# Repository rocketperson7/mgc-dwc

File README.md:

# mgc-dwc
Make Good Collective Digital White Cane

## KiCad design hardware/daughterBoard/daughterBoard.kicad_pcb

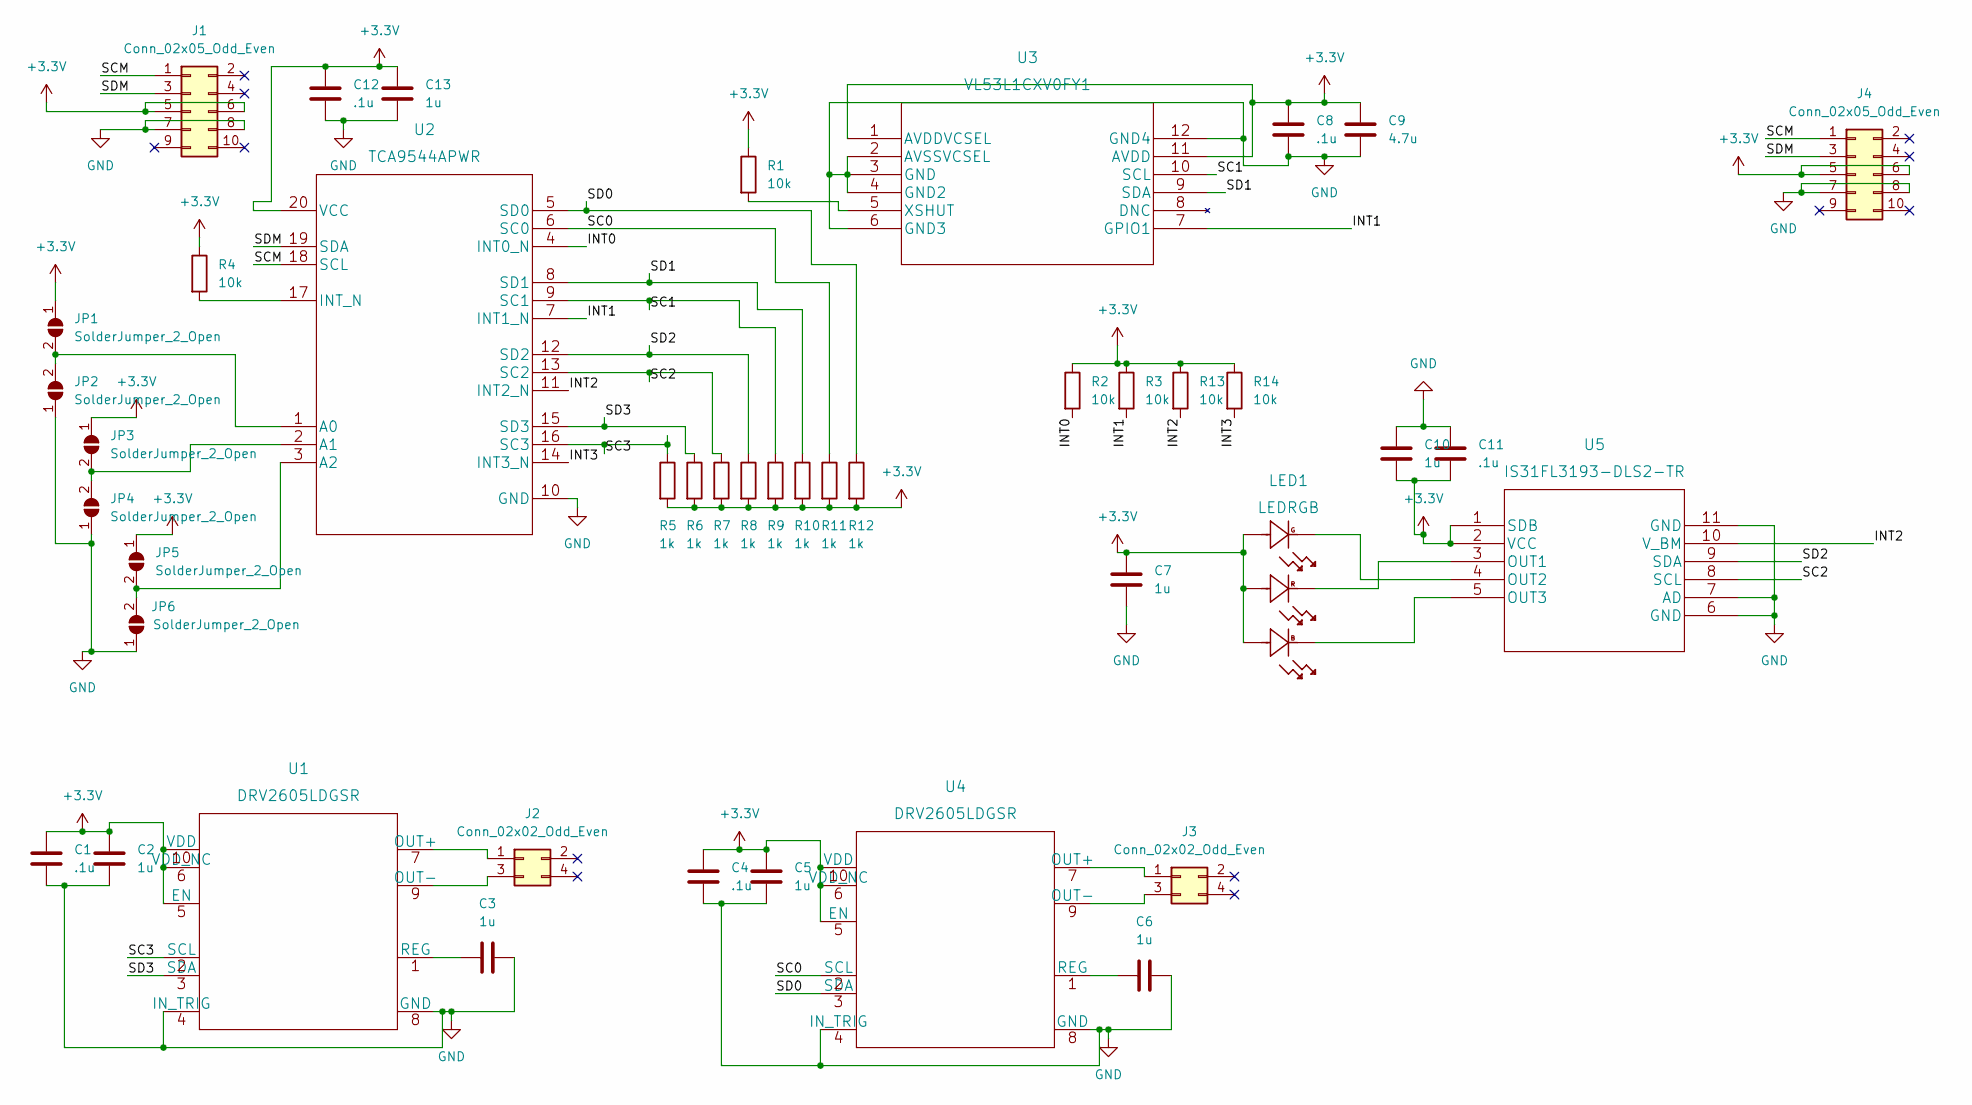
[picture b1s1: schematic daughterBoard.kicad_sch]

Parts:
C1, C4, C8, C11, C12: .1u; C_01005_0402Metric_Pad0.57x0.30mm_HandSolder
C2, C3, C5, C6, C7, C10, C13: 1u; C_01005_0402Metric_Pad0.57x0.30mm_HandSolder
C9: 4.7u; C_01005_0402Metric_Pad0.57x0.30mm_HandSolder
J1, J4: Conn_02x05_Odd_Even; PinHeader_2x05_P1.27mm_Vertical
J2, J3: Conn_02x02_Odd_Even; PinHeader_2x02_P2.54mm_Vertical
JP1, JP2, JP3, JP4, JP5, JP6: SolderJumper_2_Open; SolderJumper-2_P1.3mm_Open_TrianglePad1.0x1.5mm
LED1: LEDRGB; 150352M173300
R1, R2, R3, R4, R13, R14: 10k; R_01005_0402Metric_Pad0.57x0.30mm_HandSolder
R5, R6, R7, R8, R9, R10, R11, R12: 1k; R_01005_0402Metric_Pad0.57x0.30mm_HandSolder
U1, U4: DRV2605LDGSR
U2: TCA9544APWR
U3: VL53L1CXV0FY1; VL53L1CXV0FY&slash_1
U5: IS31FL3193-DLS2-TR

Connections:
+3V3: C1.1, C2.1, C4.1, C5.1, C7.1, C8.1, C9.1, C10.2, C11.2, C12.1, C13.1, J1.5, J1.6, J4.5, J4.6, JP1.1 (A), JP3.1 (A), JP5.1 (A), LED1.2, LED1.4, LED1.6, R1.1, R2.1, R3.1, R4.1, R5.2, R6.2, R7.2, R8.2, R9.2, R10.2, R11.2, R12.2, R13.1, R14.1, U1.5 (EN), U1.6 (VDD_NC), U1.10 (VDD), U2.20 (VCC), U3.1 (AVDDVCSEL), U3.11 (AVDD), U4.5 (EN), U4.6 (VDD_NC), U4.10 (VDD), U5.1 (SDB), U5.2 (VCC)
/INT0: R2.2, U2.4 (INT0_N)
/INT1: R3.2, U2.7 (INT1_N), U3.7 (GPIO1)
/INT2: R13.2, U2.11 (INT2_N), U5.10 (V_BM)
/INT3: R14.2, U2.14 (INT3_N)
/SC0: R11.1, U2.6 (SC0), U4.2 (SCL)
/SC1: R9.1, U2.9 (SC1), U3.10 (SCL)
/SC2: R7.1, U2.13 (SC2), U5.8 (SCL)
/SC3: R5.1, U1.2 (SCL), U2.16 (SC3)
/SCM: J1.1, J4.1, U2.18 (SCL)
/SD0: R12.1, U2.5 (SD0), U4.3 (SDA)
/SD1: R10.1, U2.8 (SD1), U3.9 (SDA)
/SD2: R8.1, U2.12 (SD2), U5.9 (SDA)
/SD3: R6.1, U1.3 (SDA), U2.15 (SD3)
/SDM: J1.3, J4.3, U2.19 (SDA)
GND: C1.2, C2.2, C3.2, C4.2, C5.2, C6.2, C7.2, C8.2, C9.2, C10.1, C11.1, C12.2, C13.2, J1.7, J1.8, J4.7, J4.8, JP2.1 (A), JP4.1 (A), JP6.1 (A), U1.4 (IN_TRIG), U1.8 (GND), U2.10 (GND), U3.2 (AVSSVCSEL), U3.3 (GND), U3.4 (GND2), U3.6 (GND3), U3.12 (GND4), U4.4 (IN_TRIG), U4.8 (GND), U5.6 (GND), U5.7 (AD), U5.11 (GND)
unnamed: C3.1, U1.1 (REG)
unnamed: C6.1, U4.1 (REG)
unnamed: J2.1, U1.7 (OUT+)
unnamed: J2.3, U1.9 (OUT-)
unnamed: J3.1, U4.7 (OUT+)
unnamed: J3.3, U4.9 (OUT-)
unnamed: JP1.2 (B), JP2.2 (B), U2.1 (A0)
unnamed: JP3.2 (B), JP4.2 (B), U2.2 (A1)
unnamed: JP5.2 (B), JP6.2 (B), U2.3 (A2)
unnamed: R1.2, U3.5 (XSHUT)
unnamed: R4.2, U2.17 (INT_N)
unnamed: LED1.3, U5.3 (OUT1)
unnamed: LED1.5, U5.4 (OUT2)
unnamed: LED1.1, U5.5 (OUT3)

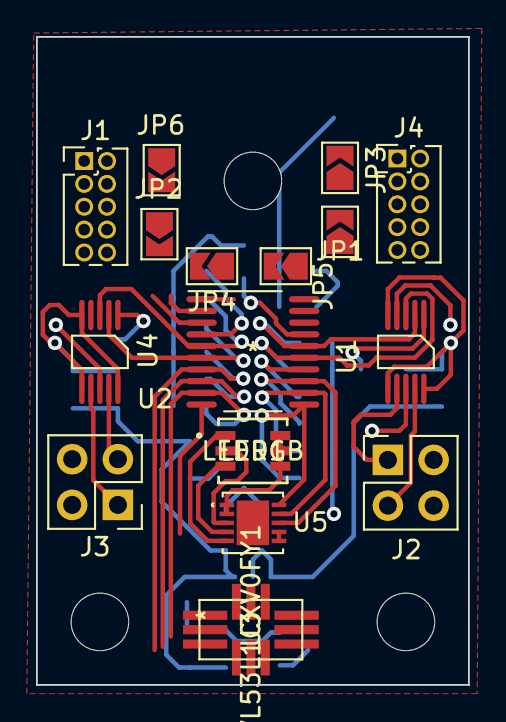
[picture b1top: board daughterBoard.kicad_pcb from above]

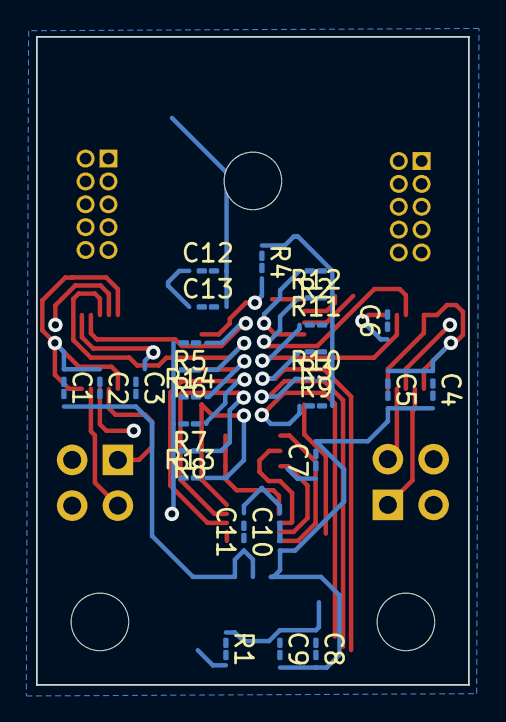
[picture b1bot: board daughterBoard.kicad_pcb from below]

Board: 4 copper layers, 24.0 x 36.0 mm, 43 parts (27 on the bottom side), 30 nets.

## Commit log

2023-03-16 create project
2023-03-20 schematic first pass
2023-03-21 edit connectors, finish annotating schematic, use all discrete resistors, assign footprints, get general board layout set
2023-03-26 v1 finished
2023-03-26 production files generated
2023-04-18 added i2c scanner program
2023-04-18 update folder structure for arduino ide
2023-04-18 add gitignore for mac os
2023-04-18 fix gitignore
2023-04-19 added super basic structure for main digital white cane firmware
2023-04-19 add datasheets
2023-05-08 fixed i2c scanner
2023-05-20 updated board files to rev2
2023-05-25 really sloppy basic example code stuck together
2023-06-05 added looping to i2c select function to turn off all other muxes.
    added looping to checking device addresses. it will not check and log all possible mux addresses
2023-06-05 quick code cleanup
2023-06-07 rough first go at reading multiple lidar and setting multiple motors
2024-05-19 modifications for hardware rev2
2024-05-27 added volume pot and button to switch between 3 different modes
2024-05-28 actually use different logic in the different modes
2024-06-09 i2c scanner updates
2025-01-28 updated i2c scanner for new mux, and added new mux testing code

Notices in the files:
parts and their libraries:
Copyright 2016 Accelerated Designs. All rights reserved.
Copyright 2021 Accelerated Designs. All rights reserved.
